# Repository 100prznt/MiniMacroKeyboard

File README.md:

# Mini Macro Keyboard (Raspberry Pi Pico)

Eine kleine USB-Makro-Tastatur auf Basis eines Raspberry Pi Pico, programmiert in
CircuitPython. Der Pico meldet sich am PC als Composite-HID-Gerät (Tastatur +
Maus gleichzeitig) und macht auf einer selbstgebauten 3-Taster-Platine ein paar
wiederkehrende Eingaben und eine kleine Anwesenheitssimulation überflüssig.

Ein Windows-Companion-Programm in C# (`MacroKeyboardSync/`) läuft im Hintergrund
und meldet dem Pico über einen zweiten USB-CDC-Kanal Uhrzeit, die aktuell aktive
Anwendung und den Sperrstatus des PCs.

## Funktionen

Die Platine hat drei Taster (M1–M3), alle gegen GND schaltend:

| Taste | Aktion |
|---|---|
| **M1** | Beim Loslassen: zweizeiliger TODO-Kommentar mit Name/Kürzel und aktuellem Zeitstempel, z. B. `// Mustermann, Max (MM/Abt1) 23.09.2026 10:23:34` gefolgt von einer leeren Kommentarzeile `// ` (Zeilenumbruch per Shift+Enter) |
| **M2** | Beim Loslassen: Text `M2` (Platzhalter, frei anpassbar) |
| **M3** | Kurzer Druck: gibt beim Loslassen die aktuell aktive Anwendung aus (siehe unten). Langer Druck (≥ 0,5 s): schaltet den Mausjiggler sofort um, ohne auf das Loslassen zu warten |
| **M1 + M3** (gleichzeitig) | Löscht per Backspace das letzte Zeichen im aktiven Feld, wartet kurz und gibt dann einen hinterlegten Text (`TEXT_M4`) + Enter aus – **nur** wenn entweder eine bestimmte Anwendung (in `code.py` festgelegt) im Vordergrund ist oder der PC gerade gesperrt ist. `M2` bleibt davon unbeteiligt |

**Mausjiggler:** Solange aktiv (Standard: direkt nach dem Einschalten), bewegt
sich der Mauszeiger alle 25 Sekunden minimal, um Bildschirmschoner/Abwesend-Status
(z. B. in Teams) zu verhindern. Die Onboard-LED pulsiert währenddessen in einem
Herzschlag-Muster (zwei Auf-/Abdimm-Pulse, kurze Pause, dann eine längere Pause).

**Status-LEDs:** Drei adressierbare RGB-LEDs (LTST-E683CEGBW) unter den Tastern,
in Reihe an GPIO18 über einen BSS138-Levelshifter angeschlossen, zeigen den
aktuellen Zustand an:
- **Aktive Anwendung:** alle drei LEDs leuchten in einer festen Farbe je nach
  `WIN:`-Tag – z. B. Lila für Visual Studio, Blau für VS Code, Orange für KiCad, Grün für den
  KiCad-PCB-Editor, Rot für Opera, Weiß für den Explorer, Blau für Outlook/Teams,
  Lila für GitHub Desktop. Unbekannte Anwendungen zeigen ein gedimmtes Grau
  (`DEFAULT`).
- **VPN-Client aktiv:** die LEDs blinken abwechselnd Rot/Blau, wie ein
  US-Polizeiauto.
- **PC gesperrt:** rotes Lauflicht über die drei LEDs (Knight-Rider-/KITT-Effekt),
  zusätzlich gedimmt gegenüber den übrigen Zuständen. Hat Vorrang vor allen
  anderen Anzeigen.

Die Helligkeit aller Status-LEDs ist über die Konstante `MAX_BRIGHTNESS` in
`code.py` gedeckelt (Standard: 65 %).

**Sync mit dem PC:** Die Companion-App erkennt über die USB-Vendor-ID automatisch
den passenden COM-Port. Da der Pico zwei COM-Ports meldet (REPL-Konsole und
Datenkanal aus `boot.py`), wird anhand der USB-Interface-Nummer gezielt der
Datenkanal gewählt – die Konsole (`MI_00`) wird nie benutzt. Fehlt `boot.py`
auf dem Pico, gibt es keinen Datenkanal und die App verbindet sich nicht. Über
den Datenkanal sendet sie dem Pico:
- `TIME:` alle 5 Minuten (stellt die Software-RTC des Pico)
- `WIN:` bei jedem Wechsel der aktiven Anwendung (VS, VS Code, KiCad, KiCad-PCB-Editor,
  Opera, Explorer, Outlook, GitHub Desktop, Teams, VPN-Client – alles andere
  als `DEFAULT`)
- `LOCK:` bei Sperren/Entsperren sowie als Heartbeat alle 15 Sekunden, damit
  der Pico eine tote Verbindung erkennt

Ohne aktuelle Nachricht vom PC (z. B. direkt nach einem Neustart, bevor die
Companion-App läuft) geht der Pico sicherheitshalber von "gesperrt" aus.

## Hardware

- Raspberry Pi Pico
- Eigene Taster-Platine mit 3 Tastern gegen GND:
  - M1 → GPIO17
  - M2 → GPIO26
  - M3 → GPIO28
- 3x adressierbare RGB-LED LTST-E683CEGBW (in Reihe), Datenleitung an GPIO18
  über einen BSS138-Levelshifter

### CAD-Ansichten

| Von oben | Von rechts |
|---|---|
|  |  |

*Rechts:* Auf der Unterseite des 3D-gedruckten Rahmens sorgen 4 Gummipuffer für einen sicheren Stand.

### Erster Hardwareaufbau

## Repo-Struktur

```
src/boot.py       Aktiviert den zweiten USB-CDC-Datenkanal (usb_cdc.data)
src/code.py       Hauptprogramm: Taster-Logik, HID-Ausgabe, Mausjiggler, Status-LEDs, Sync
src/macros.py.template  Vorlage fuer macros.py (TEXT_M2, TEXT_M4, TODO_SIGNATURE)
src/lib/          Benötigte CircuitPython-Bibliotheken (adafruit_hid, neopixel, dt. Tastaturlayout)
install/          CircuitPython-UF2 für den Pico (de_DE)
MacroKeyboardSync/ Windows-Companion-App (C#, .NET 8)
```

## Einrichtung (Pico)

1. [CircuitPython](https://circuitpython.org/board/raspberry_pi_pico/) auf den
   Pico flashen (die passende UF2-Datei liegt auch in `install/`).
2. Den Ordner `src/lib/` in den Ordner `lib/` auf dem `CIRCUITPY`-Laufwerk
   kopieren. Er enthält bereits alle benötigten Bibliotheken, sie müssen
   nicht separat heruntergeladen werden:
   - `adafruit_hid/` aus dem
     [Adafruit CircuitPython HID](https://github.com/adafruit/Adafruit_CircuitPython_HID)
   - `neopixel.mpy` aus dem
     [Adafruit CircuitPython Bundle](https://circuitpython.org/libraries)
     (steuert die drei Status-LEDs)
   - `keyboard_layout_win_de.py` und `keycode_win_de.py` (deutsches
     Tastaturlayout) aus
     [Neradoc/Circuitpython_Keyboard_Layouts](https://github.com/Neradoc/Circuitpython_Keyboard_Layouts)

   Die zugehörigen Lizenzen liegen als `LICENSE-*` daneben (beide MIT). Wer
   lieber aktuelle Versionen nutzt, kann sie stattdessen selbst aus dem
   [Adafruit CircuitPython Bundle](https://circuitpython.org/libraries) bzw.
   dem Neradoc-Repo holen.
3. `boot.py` und `code.py` aus `src/` auf das `CIRCUITPY`-Laufwerk kopieren.
4. `src/macros.py.template` nach `macros.py` kopieren (muss neben `code.py`
   liegen) und an die eigenen Texte anpassen (Name/Kürzel für M1, Text für
   die M1+M3-Combo). `macros.py` ist bewusst per `.gitignore` ausgeschlossen,
   damit persönliche Texte nicht versehentlich committet werden.

## Einrichtung (Companion-App)

1. `MacroKeyboardSync/` mit .NET 8 SDK bauen (`dotnet build` bzw. Visual
   Studio).
2. Die App beim Windows-Systemstart starten lassen (z. B. Autostart-Ordner
   oder Aufgabenplanung) – sie läuft ohne Konsolenfenster im Hintergrund.
3. Erkannte Anwendungen sind in der `KnownApps`-Dictionary in `Program.cs`
   hinterlegt und lassen sich dort um weitere Prozessnamen ergänzen. Läuft
   eine Anwendung (wie z. B. KiCad) bei dir komplett unter einem einzigen
   Prozess, wird in `GetActiveAppTag()` zusätzlich der Fenstertitel
   ausgewertet, um z. B. den PCB-Editor separat zu erkennen – Titeltext ggf.
   an die eigene Sprachversion anpassen.

## Hinweis zur M1+M3-Combo

Der bei `TEXT_M4` hinterlegte Text ist bei mir persönlich durch ein Passwort
ersetzt, das nur bei passender Anwendung bzw. gesperrtem PC getippt wird. Wer
das Repo als Vorlage nutzt: Der Wert liegt aktuell als Klartext in `macros.py`
auf dem Flash-Speicher des Pico – bei physischem Zugriff auf das Gerät ist er
auslesbar. Für den privaten Gebrauch an einem einzelnen, vertrauenswürdigen
Rechner ist das ein bewusst akzeptiertes Risiko, kein Ersatz für einen echten
Passwortmanager.

## Lizenz

Dieses Projekt steht unter der [MIT-Lizenz](LICENSE).

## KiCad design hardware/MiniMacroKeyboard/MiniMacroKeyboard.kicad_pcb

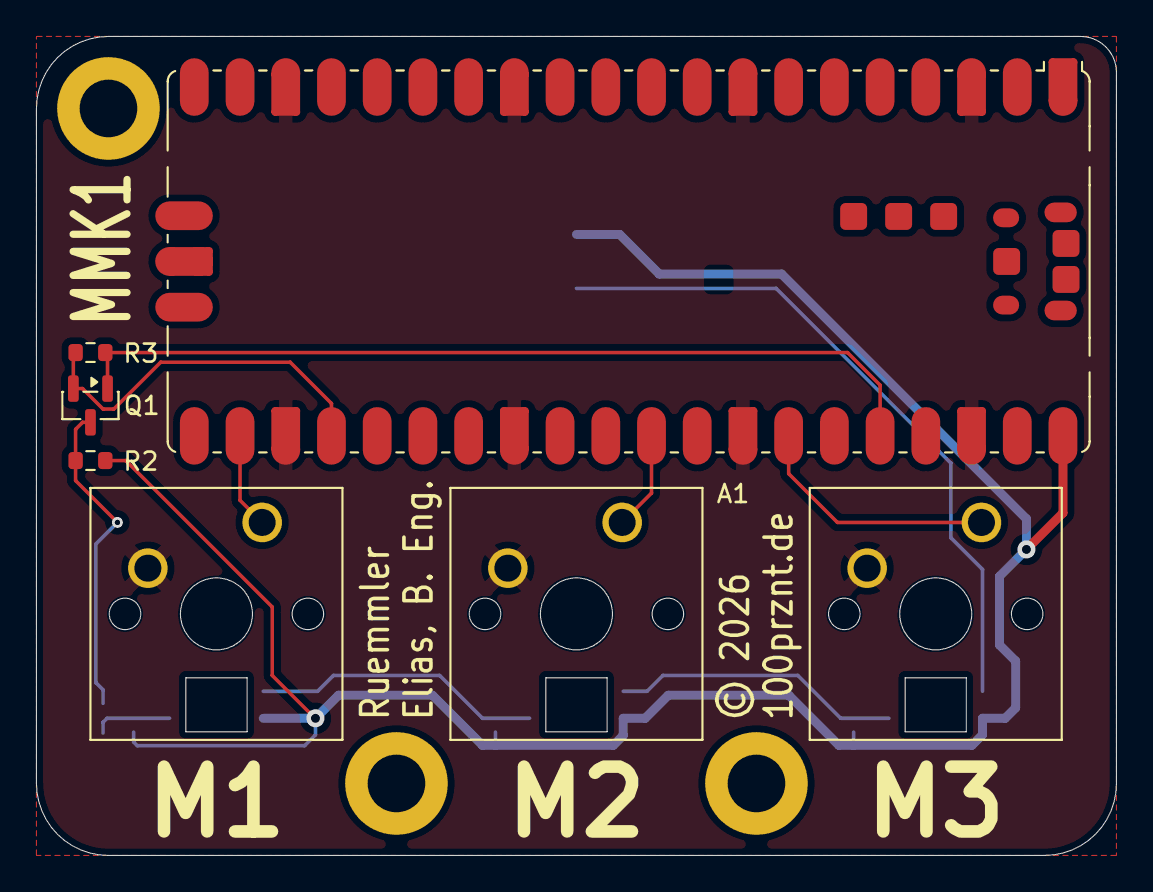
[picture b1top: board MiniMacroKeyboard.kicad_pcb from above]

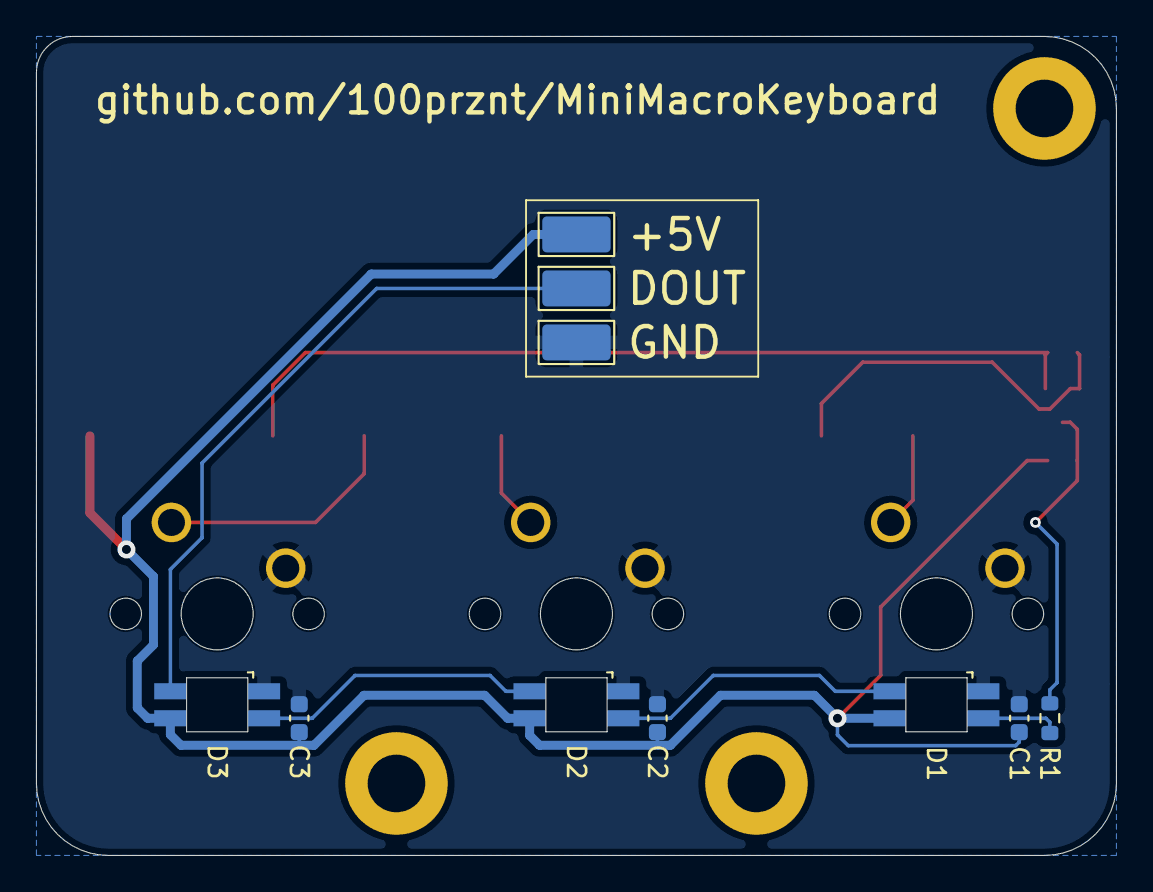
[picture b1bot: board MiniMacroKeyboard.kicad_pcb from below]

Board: 2 copper layers, 60.0 x 45.5 mm, 14 parts (7 on the bottom side), 12 nets.

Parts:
A1: RaspberryPi_Pico; RaspberryPi_Pico_SMD
C1, C2, C3: C; C_0603_1608Metric
M1, M2, M3: CherryMX_LTST-A683CEGBW; CherryMX_1.00u_PCB_LTST-A683CEGBW
Q1: BSS138; SOT-23
R1: 330R; R_0603_1608Metric
R2, R3: 10K; R_0603_1608Metric
TP1, TP2, TP3: TestPoint; TestPoint_Keystone_5019_Miniature

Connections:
+3.3V: A1.36 (3V3), Q1.1 (G), R3.2
+5V: A1.40 (VBUS), C1.1, C2.1, C3.1, M1.6 (VDD), M2.6 (VDD), M3.6 (VDD), R2.2, TP3.1 (1_1)
GNDD: A1.3 (GND), A1.8 (GND), A1.13 (GND), A1.18 (GND), A1.23 (GND), A1.28 (GND), A1.33 (AGND), A1.38 (GND), A1.D2 (GND), C1.2, C2.2, C3.2, M1.1, M1.3 (VSS), M2.1, M2.3 (VSS), M3.1, M3.3 (VSS), TP2.1 (1_1)
M1: A1.22 (GPIO17), M1.2
M2: A1.31 (GPIO26_ADC0), M2.2
M3: A1.34 (GPIO28_ADC2), M3.2
unnamed: A1.24 (GPIO18), Q1.2 (S), R3.1
unnamed: M1.4 (DIN), R1.1
unnamed: M1.5 (DOUT), M2.4 (DIN)
unnamed: M2.5 (DOUT), M3.4 (DIN)
unnamed: M3.5 (DOUT), TP1.1 (1_1)
unnamed: Q1.3 (D), R1.2, R2.1

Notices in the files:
hardware/MiniMacroKeyboard/MiniMacroKeyboard.kicad_pcb:
© 2026
